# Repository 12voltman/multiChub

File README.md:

# multiChub
USB Hubs with type-C for all ports, and variants with full programmability

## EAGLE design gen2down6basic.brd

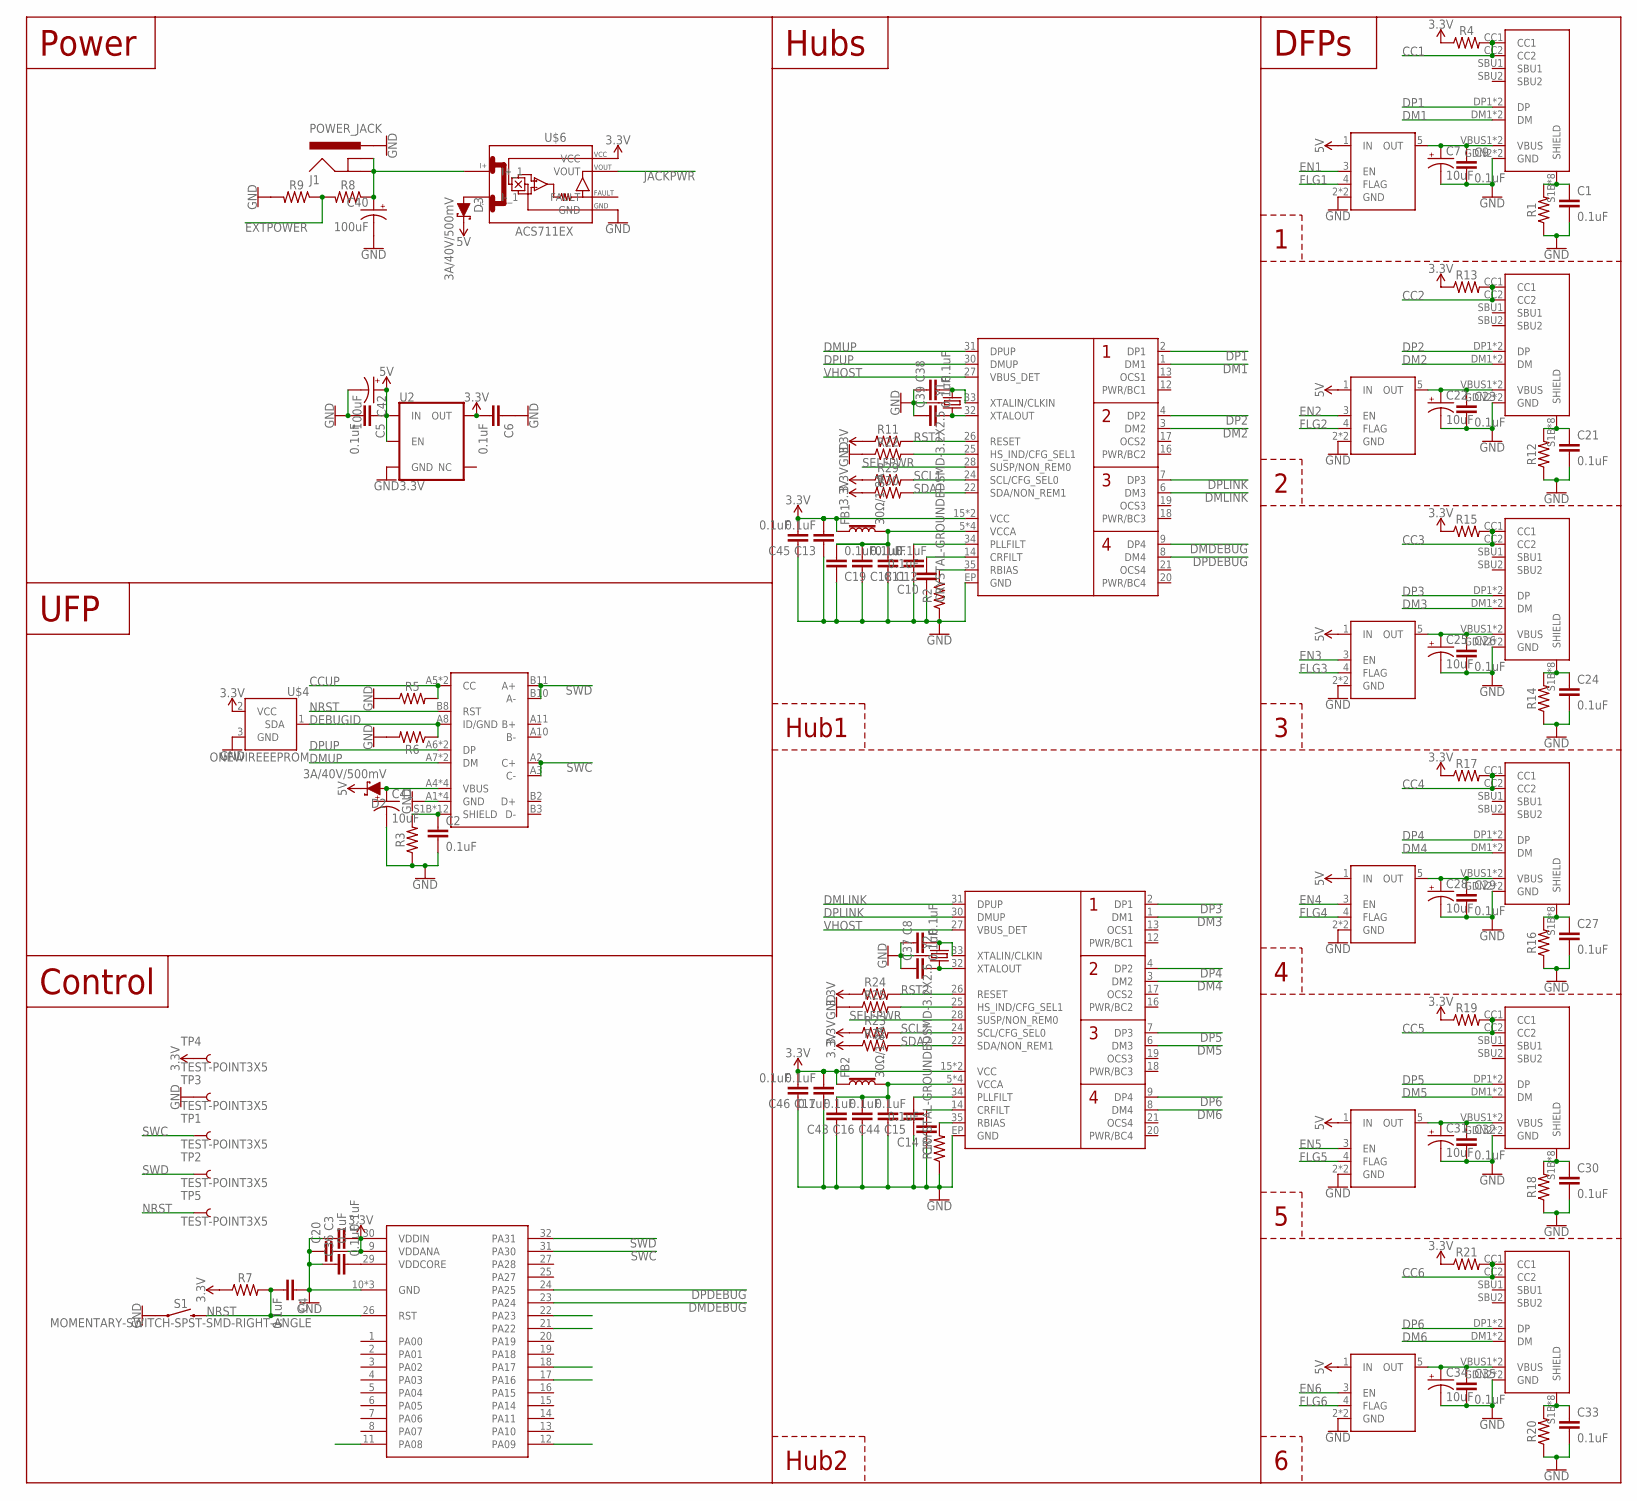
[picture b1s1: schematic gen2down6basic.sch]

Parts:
C1, C2, C3, C4, C5, C6, C8, C9, C10, C11, C12, C13, C14, C15, C16, C17, C18, C19, C20, C21, C23, C24, C26, C27, C29, C30, C32, C33, C35, C36, C37, C38, C39, C43, C44, C45, C46: 0.1uF; 0603
C7, C22, C25, C28, C31, C34, C41: 10uF; CPOL-RADIAL-2.5MM-5MM
C40, C42: 100uF; CPOL-RADIAL-2.5MM-6.5MM
D2, D3: 3A/40V/500mV; SMA-DIODE
FB1, FB2: 30Ω/1.8A; 0603
J1: POWER_JACK; POWER_JACK_PTH
R1, R2, R3, R4, R5, R6, R7, R8, R9, R10, R11, R12, R13, R14, R15, R16, R17, R18, R19, R20, R21, R22, R23, R24, R25, R29, R30, R32: 0603
S1: MOMENTARY-SWITCH-SPST-SMD-RIGHT-ANGLE; TACTILE_SWITCH_SMD_RIGHT_ANGLE
TP1, TP2, TP3, TP4, TP5: TEST-POINT3X5; PAD.03X.05
U2: 3.3V; SOT23-5
U$1, U$11, U$13, U$15, U$17, U$19: AP22804/14*SN; UDFN2020-6-EP
U$2: USB-C_DEBUG-HORZ-F; USB-C_24PIN_HORZ-F-UNTESTED
U$3, U$10, U$12, U$14, U$16, U$18: USB-C_USB2ONLY-HORZ-F_12P; USB-C_12PIN_HORZ-F
U$4: ONEWIREEEPROM; SOT23-3
U$5, U$7: USB2512/3/4; QFN36_6X6
U$6: ACS711EX; QFN12_3X3-CURRENT
U$8: ATSAMD2E1A-M; QFN32_5X5
Y1, Y2: CRYSTAL-GROUNDEDSMD-3.2X2.5; CRYSTAL-SMD-3.2X2.5MM

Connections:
3.3V: C3.2, C6.2, C13.2, C17.2, C20.2, C45.2, C46.2, FB1.1, FB2.1, R4.1, R7.1, R11.1, R13.1, R15.1, R17.1, R19.1, R21.1, R23.1, R24.1, R29.1, R30.1, R32.1, TP4.P$1, U2.5 (OUT), U$4.2 (VCC), U$5.15 (VCC), U$5.23 (VCC), U$6.P$10 (VCC), U$7.15 (VCC), U$7.23 (VCC), U$8.9 (VDDANA), U$8.30 (VDDIN)
5V: C5.1, C42.1 (+), D2.C, D3.C, U2.1 (IN), U2.3 (EN), U$1.1 (IN), U$11.1 (IN), U$13.1 (IN), U$15.1 (IN), U$17.1 (IN), U$19.1 (IN)
BIAS1: R2.2, U$5.35 (RBIAS)
BIAS2: R10.2, U$7.35 (RBIAS)
CC1: R4.2, U$3.CC1, U$3.CC2
CC2: R13.2, U$10.CC1, U$10.CC2
CC3: R15.2, U$12.CC1, U$12.CC2
CC4: R17.2, U$14.CC1, U$14.CC2
CC5: R19.2, U$16.CC1, U$16.CC2
CC6: R21.2, U$18.CC1, U$18.CC2
CCUP: R5.2, U$2.A5 (CC), U$2.B5 (CC)
CR1: C10.2, U$5.14 (CRFILT)
CR2: C14.2, U$7.14 (CRFILT)
DEBUGID: R6.1, U$2.A8 (ID/GND), U$4.1 (SDA)
DM1: U$3.DM1 (DM), U$3.DM2 (DM), U$5.1 (DM1)
DM2: U$5.3 (DM2), U$10.DM1 (DM), U$10.DM2 (DM)
DM3: U$7.1 (DM1), U$12.DM1 (DM), U$12.DM2 (DM)
DM4: U$7.3 (DM2), U$14.DM1 (DM), U$14.DM2 (DM)
DM5: U$7.6 (DM3), U$16.DM1 (DM), U$16.DM2 (DM)
DM6: U$7.8 (DM4), U$18.DM1 (DM), U$18.DM2 (DM)
DMDEBUG: U$5.9 (DP4), U$8.23 (PA24)
DMLINK: U$5.6 (DM3), U$7.31 (DPUP)
DMUP: U$2.A7 (DM), U$2.B7 (DM), U$5.31 (DPUP)
DP1: U$3.DP1 (DP), U$3.DP2 (DP), U$5.2 (DP1)
DP2: U$5.4 (DP2), U$10.DP1 (DP), U$10.DP2 (DP)
DP3: U$7.2 (DP1), U$12.DP1 (DP), U$12.DP2 (DP)
DP4: U$7.4 (DP2), U$14.DP1 (DP), U$14.DP2 (DP)
DP5: U$7.7 (DP3), U$16.DP1 (DP), U$16.DP2 (DP)
DP6: U$7.9 (DP4), U$18.DP1 (DP), U$18.DP2 (DP)
DPDEBUG: U$5.8 (DM4), U$8.24 (PA25)
DPLINK: U$5.7 (DP3), U$7.30 (DMUP)
DPUP: U$2.A6 (DP), U$2.B6 (DP), U$5.30 (DMUP)
EN1: U$1.3 (EN)
EN2: U$11.3 (EN)
EN3: U$13.3 (EN)
EN4: U$15.3 (EN)
EN5: U$17.3 (EN)
EN6: U$19.3 (EN)
EXTPOWER: R8.2, R9.1
FLG1: U$1.4 (FLAG)
FLG2: U$11.4 (FLAG)
FLG3: U$13.4 (FLAG)
FLG4: U$15.4 (FLAG)
FLG5: U$17.4 (FLAG)
FLG6: U$19.4 (FLAG)
GND: C1.2, C2.2, C3.1, C4.1, C5.2, C6.1, C7.2 (-), C8.1, C9.2, C10.1, C11.1, C12.1, C13.1, C14.1, C15.1, C16.1, C17.1, C18.1, C19.1, C20.1, C21.2, C22.2 (-), C23.2, C24.2, C25.2 (-), C26.2, C27.2, C28.2 (-), C29.2, C30.2, C31.2 (-), C32.2, C33.2, C34.2 (-), C35.2, C36.1, C37.1, C38.1, C39.1, C40.2 (-), C41.2 (-), C42.2 (-), C43.1, C44.1, C45.1, C46.1, J1.PWR, R1.1, R2.1, R3.1, R5.1, R6.2, R9.2, R10.1, R12.1, R14.1, R16.1, R18.1, R20.1, R22.1, R25.1, S1.1, TP3.P$1, U2.2 (GND), U$1.2 (GND), U$1.EP (GND), U$2.A1 (GND), U$2.A12 (GND), U$2.B1 (GND), U$2.B12 (GND), U$3.GDN2 (GND), U$3.GND1 (GND), U$4.3 (GND), U$5.EP (GND), U$6.P$3 (GND), U$7.EP (GND), U$8.10 (GND), U$8.28 (GND), U$8.GND, U$10.GDN2 (GND), U$10.GND1 (GND), U$11.2 (GND), U$11.EP (GND), U$12.GDN2 (GND), U$12.GND1 (GND), U$13.2 (GND), U$13.EP (GND), U$14.GDN2 (GND), U$14.GND1 (GND), U$15.2 (GND), U$15.EP (GND), U$16.GDN2 (GND), U$16.GND1 (GND), U$17.2 (GND), U$17.EP (GND), U$18.GDN2 (GND), U$18.GND1 (GND), U$19.2 (GND), U$19.EP (GND), Y1.2 (3), Y1.4 (3), Y2.2 (3), Y2.4 (3)
JACKPWR: U$6.P$9 (VOUT)
unnamed: D3.A, U$6.P$2 (I-_1)
unnamed: C36.2, U$8.29 (VDDCORE)
unnamed: R22.2, U$5.25 (HS_IND/CFG_SEL1)
unnamed: R25.2, U$7.25 (HS_IND/CFG_SEL1)
NRST: C4.2, R7.2, S1.2, TP5.P$1, U$2.B8 (RST), U$8.26 (RST)
PLL1: C11.2, U$5.34 (PLLFILT)
PLL2: C15.2, U$7.34 (PLLFILT)
RST1: R11.2, U$5.26 (RESET)
RST2: R24.2, U$7.26 (RESET)
SCL1: R29.2, U$5.24 (SCL/CFG_SEL0)
SCL2: R23.2, U$7.24 (SCL/CFG_SEL0)
SDA1: R30.2, U$5.22 (SDA/NON_REM1)
SDA2: R32.2, U$7.22 (SDA/NON_REM1)
SELFPWR: U$5.28 (SUSP/NON_REM0), U$7.28 (SUSP/NON_REM0)
SHIELD1: C1.1, R1.2, U$3.S1B (SHIELD), U$3.S1T (SHIELD), U$3.S2B (SHIELD), U$3.S2T (SHIELD), U$3.S3B (SHIELD), U$3.S3T (SHIELD), U$3.S4B (SHIELD), U$3.S4T (SHIELD)
SHIELD2: C21.1, R12.2, U$10.S1B (SHIELD), U$10.S1T (SHIELD), U$10.S2B (SHIELD), U$10.S2T (SHIELD), U$10.S3B (SHIELD), U$10.S3T (SHIELD), U$10.S4B (SHIELD), U$10.S4T (SHIELD)
SHIELD3: C24.1, R14.2, U$12.S1B (SHIELD), U$12.S1T (SHIELD), U$12.S2B (SHIELD), U$12.S2T (SHIELD), U$12.S3B (SHIELD), U$12.S3T (SHIELD), U$12.S4B (SHIELD), U$12.S4T (SHIELD)
SHIELD4: C27.1, R16.2, U$14.S1B (SHIELD), U$14.S1T (SHIELD), U$14.S2B (SHIELD), U$14.S2T (SHIELD), U$14.S3B (SHIELD), U$14.S3T (SHIELD), U$14.S4B (SHIELD), U$14.S4T (SHIELD)
SHIELD5: C30.1, R18.2, U$16.S1B (SHIELD), U$16.S1T (SHIELD), U$16.S2B (SHIELD), U$16.S2T (SHIELD), U$16.S3B (SHIELD), U$16.S3T (SHIELD), U$16.S4B (SHIELD), U$16.S4T (SHIELD)
SHIELD6: C33.1, R20.2, U$18.S1B (SHIELD), U$18.S1T (SHIELD), U$18.S2B (SHIELD), U$18.S2T (SHIELD), U$18.S3B (SHIELD), U$18.S3T (SHIELD), U$18.S4B (SHIELD), U$18.S4T (SHIELD)
SHIELDUP: C2.1, R3.2, U$2.S1B (SHIELD), U$2.S1T (SHIELD), U$2.S2B (SHIELD), U$2.S2T (SHIELD), U$2.S3B (SHIELD), U$2.S3T (SHIELD), U$2.S4B (SHIELD), U$2.S4T (SHIELD), U$2.S5B (SHIELD), U$2.S5T (SHIELD), U$2.S6B (SHIELD), U$2.S6T (SHIELD)
SWC: TP1.P$1, U$2.A2 (C+), U$2.A3 (C-), U$8.31 (PA30)
SWD: TP2.P$1, U$2.B10 (A-), U$2.B11 (A+), U$8.32 (PA31)
VCCA1: C12.2, C18.2, C19.2, FB1.2, U$5.5 (VCCA), U$5.10 (VCCA), U$5.29 (VCCA), U$5.36 (VCCA)
VCCA2: C16.2, C43.2, C44.2, FB2.2, U$7.5 (VCCA), U$7.10 (VCCA), U$7.29 (VCCA), U$7.36 (VCCA)
VHOST: C41.1 (+), D2.A, U$2.A4 (VBUS), U$2.A9 (VBUS), U$2.B4 (VBUS), U$2.B9 (VBUS), U$5.27 (VBUS_DET), U$7.27 (VBUS_DET)
VIN: C40.1 (+), J1.GND, J1.GNDBREAK, R8.1, U$6.P$1 (I+_1)
VOUT1: C7.1 (+), C9.1, U$1.5 (OUT), U$3.VBUS1 (VBUS), U$3.VBUS2 (VBUS)
VOUT2: C22.1 (+), C23.1, U$10.VBUS1 (VBUS), U$10.VBUS2 (VBUS), U$11.5 (OUT)
VOUT3: C25.1 (+), C26.1, U$12.VBUS1 (VBUS), U$12.VBUS2 (VBUS), U$13.5 (OUT)
VOUT4: C28.1 (+), C29.1, U$14.VBUS1 (VBUS), U$14.VBUS2 (VBUS), U$15.5 (OUT)
VOUT5: C31.1 (+), C32.1, U$16.VBUS1 (VBUS), U$16.VBUS2 (VBUS), U$17.5 (OUT)
VOUT6: C34.1 (+), C35.1, U$18.VBUS1 (VBUS), U$18.VBUS2 (VBUS), U$19.5 (OUT)
XIN1: C38.2, U$5.33 (XTALIN/CLKIN), Y1.1
XIN2: C8.2, U$7.33 (XTALIN/CLKIN), Y2.1
XOUT1: C39.2, U$5.32 (XTALOUT), Y1.3 (2)
XOUT2: C37.2, U$7.32 (XTALOUT), Y2.3 (2)

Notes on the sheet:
DFPs
UFP
Power
Hubs
Control
Hub1
Hub2

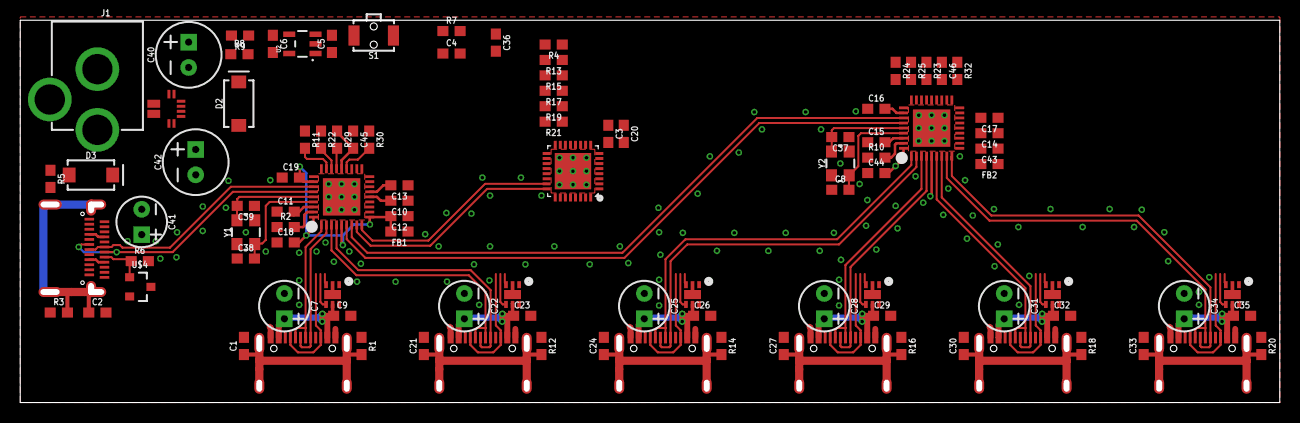
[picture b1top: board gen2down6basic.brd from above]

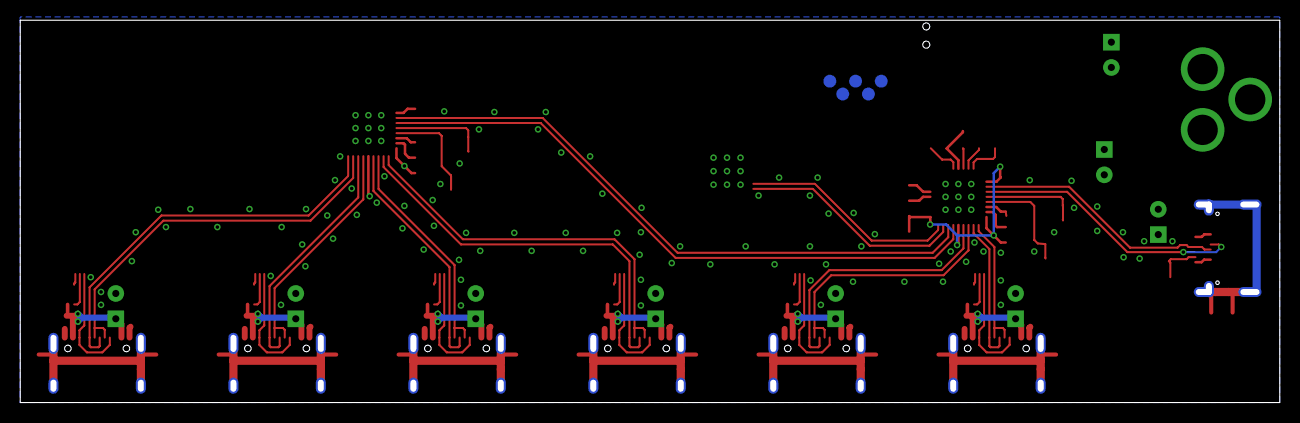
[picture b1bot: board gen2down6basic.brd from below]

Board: 2 copper layers, 124.4 x 37.8 mm, 106 parts (5 on the bottom side), 71 nets.

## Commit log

2019-03-09 Initial upload of 6 port 2.0 hub with programmability

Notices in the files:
parts and their libraries:
SparkFun-DiscreteSemi: Licensing: Creative Commons ShareAlike 4.0 International - https://creativecommons.org/licenses/by-sa/4.0
